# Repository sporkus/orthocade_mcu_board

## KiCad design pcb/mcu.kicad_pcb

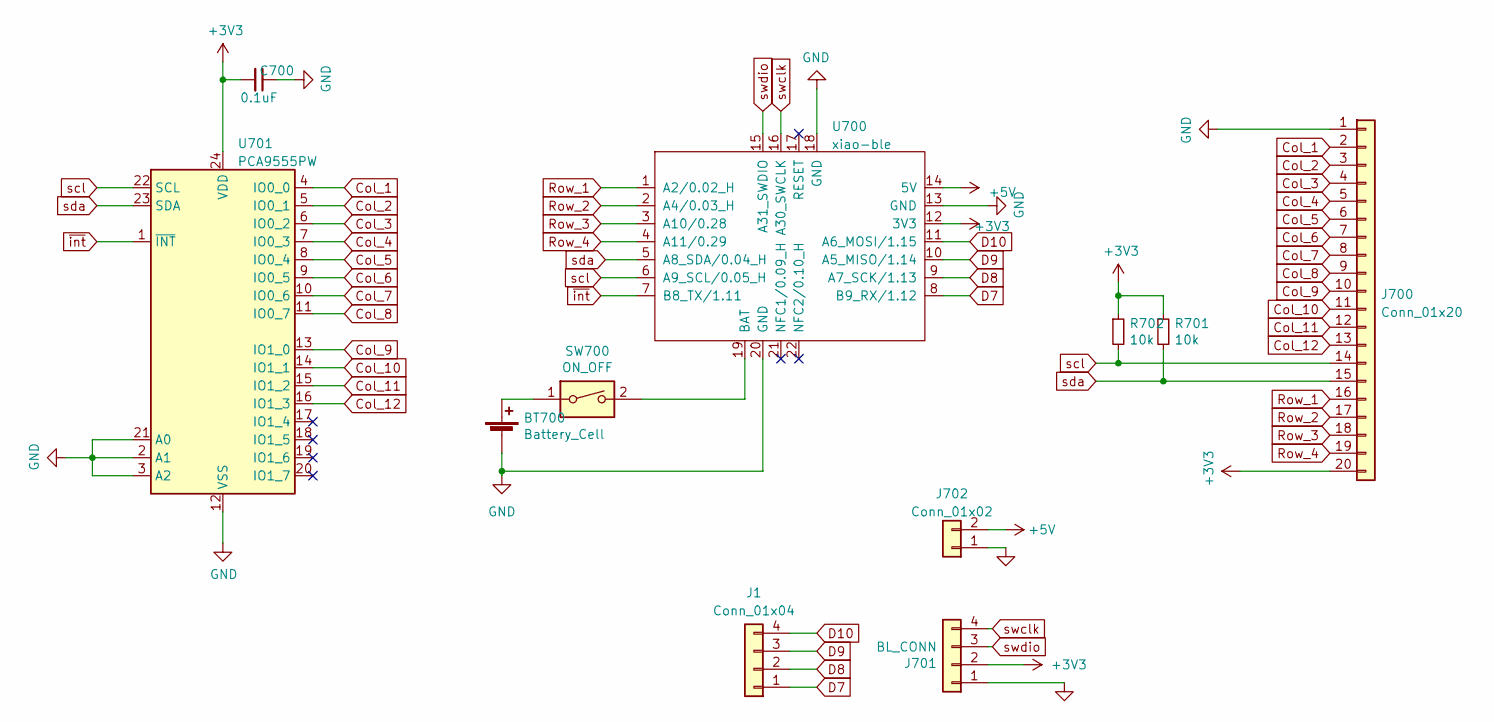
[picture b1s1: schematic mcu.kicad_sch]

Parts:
BT700: Battery_Cell; PinHeader_1x02_P2.00mm_Vertical
C700: 0.1uF; C_0805_2012Metric
J1: Conn_01x04; PinHeader_2x02_P2.00mm_Horizontal
J700: Conn_01x20; FCC 20pin
J701: BL_CONN; PinHeader_1x04_P2.54mm_Vertical
J702: Conn_01x02; PinHeader_1x02_P2.54mm_Vertical
R701, R702: 10k; R_0805_2012Metric_Pad1.20x1.40mm_HandSolder
SW700: ON_OFF; switch_MSK-12C02_smd
U700: xiao-ble; xiao-ble-smd-cutout
U701: PCA9555PW; TSSOP-24_4.4x7.8mm_P0.65mm

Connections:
+3V3: C700.2, J700.20, J701.2, R701.1, R702.1, U700.12 (3V3), U701.24 (VDD)
+5V: J702.2, U700.14 (5V)
Col_1: J700.2, U701.4 (IO0_0)
Col_2: J700.3, U701.5 (IO0_1)
Col_3: J700.4, U701.6 (IO0_2)
Col_4: J700.5, U701.7 (IO0_3)
Col_5: J700.6, U701.8 (IO0_4)
Col_6: J700.7, U701.9 (IO0_5)
Col_7: J700.8, U701.10 (IO0_6)
Col_8: J700.9, U701.11 (IO0_7)
Col_9: J700.10, U701.13 (IO1_0)
Col_10: J700.11, U701.14 (IO1_1)
Col_11: J700.12, U701.15 (IO1_2)
Col_12: J700.13, U701.16 (IO1_3)
D7: J1.1, U700.8 (B9_RX/1.12)
D8: J1.2, U700.9 (A7_SCK/1.13)
D9: J1.3, U700.10 (A5_MISO/1.14)
D10: J1.4, U700.11 (A6_MOSI/1.15)
GND: BT700.2 (-), C700.1, J700.1, J701.1, J702.1, U700.13 (GND), U700.18 (GND), U700.20 (GND), U701.2 (A1), U701.3 (A2), U701.12 (VSS), U701.21 (A0); also elsewhere on the board
unnamed 19: BT700.1 (+), SW700.1; also elsewhere on the board
unnamed: SW700.2, U700.19 (BAT)
Row_1: J700.16, U700.1 (A2/0.02_H)
Row_2: J700.17, U700.2 (A4/0.03_H)
Row_3: J700.18, U700.3 (A10/0.28)
Row_4: J700.19, U700.4 (A11/0.29)
scl: J700.14, R702.2, U700.6 (A9_SCL/0.05_H), U701.22 (SCL)
sda: J700.15, R701.2, U700.5 (A8_SDA/0.04_H), U701.23 (SDA)
swclk: J701.4, U700.16 (A30_SWCLK)
swdio: J701.3, U700.15 (A31_SWDIO)
~int: U700.7 (B8_TX/1.11), U701.1 (~INT)

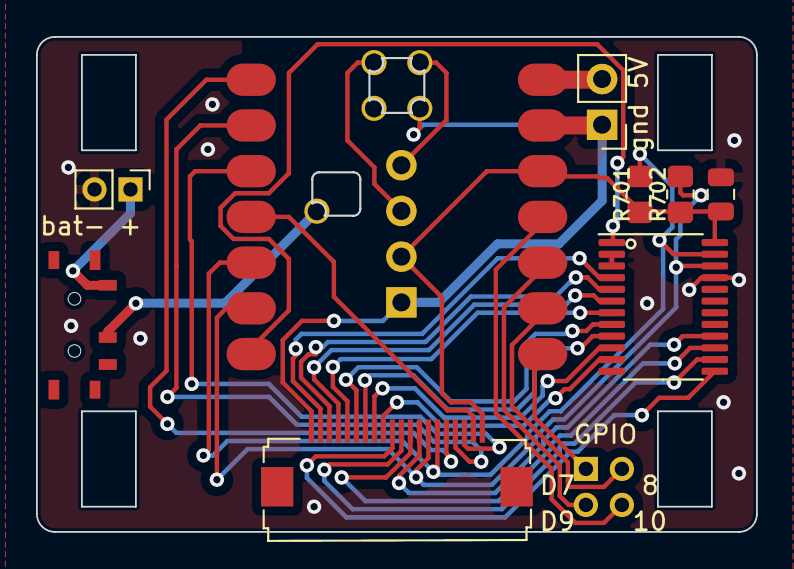
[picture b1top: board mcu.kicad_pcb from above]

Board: 2 copper layers, 40.0 x 27.5 mm, 11 parts (1 on the bottom side), 30 nets.

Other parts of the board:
bat- +: Battery_Cell; PinHeader_1x02_P2.00mm_Vertical

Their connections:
GND: bat- +.2 (-); also elsewhere on the board
unnamed 19: bat- +.1 (+); also elsewhere on the board

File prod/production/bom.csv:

Designator,Footprint,Quantity,Value,LCSC Part #
C700,0805,1,0.1uF,
J1,PinHeader_2x02_P2.00mm_Horizontal,1,Conn_01x04,
J700,FCC 20pin,1,Conn_01x20,
J701,PinHeader_1x04_P2.54mm_Vertical,1,BL_CONN,
J702,PinHeader_1x02_P2.54mm_Vertical,1,Conn_01x02,
"R701, R702",0805,2,10k,
SW700,switch_MSK-12C02_smd,1,ON_OFF,
U700,xiao-ble-smd-cutout,1,xiao-ble,
U701,TSSOP-24_4.4x7.8mm_P0.65mm,1,PCA9555PW,
bat- +,PinHeader_1x02_P2.00mm_Vertical,1,Battery_Cell,

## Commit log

2023-04-27 Added interrupt lines and GPIO breakout
